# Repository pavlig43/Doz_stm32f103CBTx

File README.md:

# Дозатор: F103 и F030

Общая логика лежит в `app/` и `lib/`. Весь проект CubeMX для каждого МК хранится в своей папке.

```text
app/                         общая логика
lib/                         общие заголовки и модули
  fee/fee.h                  общий интерфейс памяти
  fee/fee.c                  общий модуль памяти
  enc/enc.h                  общий интерфейс энкодера
  enc/enc.c                  общий модуль энкодера
  hx/hx.h, hx/hx.c            один общий модуль HX711
stm32f103/                   проект CubeMX и сборка F103
stm32f030/                   проект CubeMX и сборка F030
kicad/                       проект платы, библиотеки, модели и PDF для ЛУТ
CMakeLists.txt               сборка из корня для CLion
CMakePresets.json            профили F103 и F030
```

В `stm32f103/` находятся `.ioc`, `.mxproject`, `Core/`, `Drivers/`, `cmake/`, файл запуска, файл памяти, `CMakeLists.txt` и `CMakePresets.json`. Корень Git, `app/` и `lib/` остаются общими. Старый `build/` в корне не перенесён; новые сборки пишутся в `stm32f103/build/`.

## Сборка F103

Нужны CMake 3.22+, Ninja и Arm GNU Toolchain (`arm-none-eabi-*`) в `PATH`. В CLion работайте в прежнем корне репозитория. Корневой CMake подключает проект выбранного МК; общий код остаётся виден в том же окне. В `.idea/cmake.xml` сохранены профили F103 Debug, F103 Release, F030 Debug и F030 Release для набора инструментов STM32. Общие файлы уже включены в обе цели; добавлять их вручную не нужно. Для командной строки профили называются Debug, Release, F030-Debug и F030-Release. Переключать папки не нужно. Обе платы запускают общий код дозатора.

```powershell
cmake --preset Debug
cmake --build --preset Debug
cmake --preset Release
cmake --build --preset Release
```

При сборке из корня результаты лежат в `stm32f103/build/CLion-Debug` и `stm32f103/build/CLion-Release`; файлы `.elf` — в их подпапке `stm32f103`. Для F030 используются свои каталоги `stm32f030/build/CLion-*`. Каждый проект также можно собирать отдельно его прежними профилями из папки МК. Общие исходники и пути к заголовкам явно заданы в `stm32f103/CMakeLists.txt`. Обе сборки подключают общие `lib/enc/enc.c` и `lib/fee/fee.c`. В блоке `USER CODE` файла `Core/Inc/tim.h` каждой платы задан `ENC_TIMER`: `htim2` для F103 и `htim3` для F030. В `Core/Inc/main.h` задан `EEPROM_START_ADDR`: `0x0800FC00U` для F103 и `0x08003C00U` для F030. Размер страницы FEE — 1 КБ у обеих плат; в файле памяти F030 для кода оставлено 15 КБ.

## CubeMX и общий код

Открывайте `stm32f103/Doz_stm32f103CBTx.ioc` отдельно. При генерации каталог проекта должен быть `stm32f103`, путь к `main.c` — `Core/Src`, инструмент сборки — CMake. Не выбирайте корень репозитория как каталог вывода. `cmake/stm32cubemx/CMakeLists.txt` внутри проекта принадлежит CubeMX; общие файлы подключайте только в проектном `CMakeLists.txt`. Пользовательский код в `Core/` храните в блоках `USER CODE`.

Для штатного CLI CubeMX загружайте перенесённый `.ioc` и сразу запускайте генерацию; отдельная команда `project path` в CubeMX 6.18 добавляет вложенную папку с именем проекта:

```text
config load <полный путь>/stm32f103/Doz_stm32f103CBTx.ioc
project generate
exit
```

Передавайте такой файл команд в CubeMX через `-q`. На изолированной копии проверены генерация и обе сборки: общие файлы, `USER CODE`, CMake и настройки компилятора сохранены. CubeMX объединяет запись начального низкого уровня `Motor_Pin` с остальными выводами GPIOA; поведение не меняется. Ручной комментарий вне `USER CODE` при этом теряется. Исходный `gpio.c` в этом дереве сохранён.

Для F030 уже создан отдельный `stm32f030/stm32f030.ioc`. CubeMX каждого проекта должен писать только в папку своего МК; `app/`, `lib/` и корневой CMake он не должен менять.

Общие модули получают HAL из проектных `main.h`, `tim.h`, `i2c.h`. Обе платы должны дать сигналы `SCK`, `DOUT`, `Motor`, `R`, `G`, `B`, `Enc_But`, дескриптор `hi2c1` для LCD и `htim1` с шагом счётчика 1 мкс для HX711. Выводы F030 выбираются по схеме.

Код дозатора подключён к F030: в `main.c` добавлены запуск модулей и основной цикл. Debug для F030 использует `-Og`, чтобы код вместе с HAL поместился в 15 КБ Flash; сведения для отладки сохранены. Сборки и расход памяти описаны в [инструкции F030](stm32f030/README.md). Работа на плате ещё требует проверки.

## Проект платы

Текущий проект KiCad хранится вместе с прошивкой: [kicad/doz_030.kicad_pro](kicad/doz_030.kicad_pro). После клонирования или `git pull` открывайте этот файл в KiCad 10. Схема, плата, настройки проекта, нужные библиотеки и 3D-модели находятся в репозитории. Пути к местным библиотекам и моделям заданы через `${KIPRJMOD}` и не зависят от прежнего каталога на компьютере.

PDF для ЛУТ и порядок его сборки описаны в [kicad/README.md](kicad/README.md). Устаревшая папка `hardware` удалена; рабочие правки платы нужно делать только в `kicad/`.

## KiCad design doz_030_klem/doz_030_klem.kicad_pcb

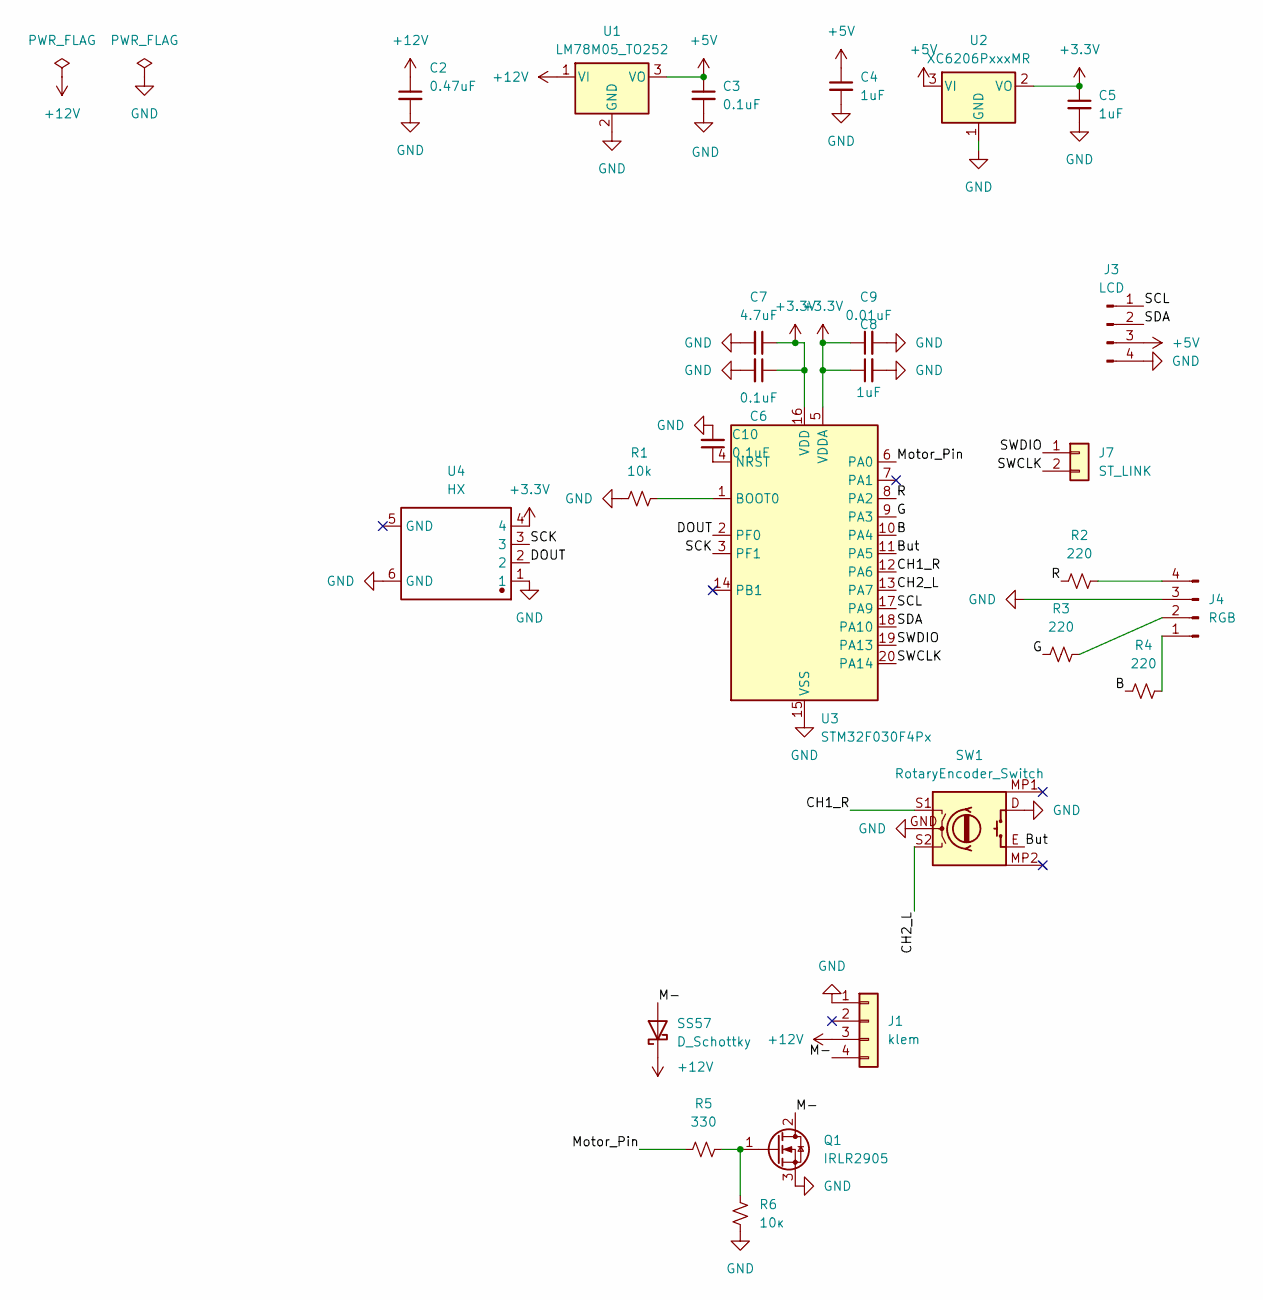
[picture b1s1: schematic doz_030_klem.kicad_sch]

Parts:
C2: 0.47uF; C_1206_3216Metric; Voltage 16V; Tolerance 20%
C3, C6, C10: 0.1uF; C_1206_3216Metric; Voltage 16V; Tolerance 20%
C4, C5, C8: 1uF; C_1206_3216Metric; Voltage 16V; Tolerance 20%
C7: 4.7uF; C_1206_3216Metric; Voltage 16V; Tolerance 20%
C9: 0.01uF; C_1206_3216Metric; Voltage 16V; Tolerance 20%
J1: klem; TerminalBlock_MaiXu_MX126-5.0-04P_1x04_P5.00mm
J3: LCD; PinHeader_1x04_P2.54mm_Vertical
J4: RGB; PinHeader_1x04_P2.54mm_Vertical
J7: ST_LINK; PinHeader_1x02_P2.54mm_Vertical
Q1: IRLR2905; TO-252-2
R1: 10k; R_1206_3216Metric
R2, R3, R4: 220; R_1206_3216Metric
R5: 330; R_1206_3216Metric
R6: 10к; R_1206_3216Metric
SS57: D_Schottky; D_SMC
SW1: RotaryEncoder_Switch; EC11_MY
U1: LM78M05_TO252; TO-252-2
U2: XC6206PxxxMR; SOT-23-3
U3: STM32F030F4Px; TSSOP-20_4.4x6.5mm_P0.65mm
U4: HX; USB_A_TH_MOLEX_67643_3910; Manufacturer Part 67643-3910

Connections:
+3.3V: C5.1, C6.1, C7.1, C8.1, C9.1, U2.2 (VO), U3.5 (VDDA), U3.16 (VDD), U4.4
+5V: C3.1, C4.1, J3.3, U1.3 (VO), U2.3 (VI)
+12V: C2.1, J1.3, SS57.1 (K), U1.1 (VI)
/B: R4.1, U3.10 (PA4)
/But: SW1.E, U3.11 (PA5)
/CH1_R: SW1.S1, U3.12 (PA6)
/CH2_L: SW1.S2, U3.13 (PA7)
/DOUT: U3.2 (PF0), U4.2
/G: R3.1, U3.9 (PA3)
/M-: J1.4, Q1.2 (D), SS57.2 (A)
/Motor_Pin: R5.1, U3.6 (PA0)
/R: R2.1, U3.8 (PA2)
/SCK: U3.3 (PF1), U4.3
/SCL: J3.1, U3.17 (PA9)
/SDA: J3.2, U3.18 (PA10)
/SWCLK: J7.2, U3.20 (PA14); also elsewhere on the board
/SWDIO: J7.1, U3.19 (PA13); also elsewhere on the board
GND: C2.2, C3.2, C4.2, C5.2, C6.2, C7.2, C8.2, C9.2, C10.2, J1.1, J3.4, J4.3, Q1.3 (S), R1.1, R6.1, SW1.D, SW1.GND, U1.2 (GND), U2.1 (GND), U3.15 (VSS), U4.1, U4.6 (GND)
unnamed: J4.1, R4.2
unnamed: J4.2, R3.2
unnamed: J4.4, R2.2
unnamed: Q1.1 (G), R5.2, R6.2
unnamed: R1.2, U3.1 (BOOT0)
unnamed: C10.1, U3.4 (NRST)

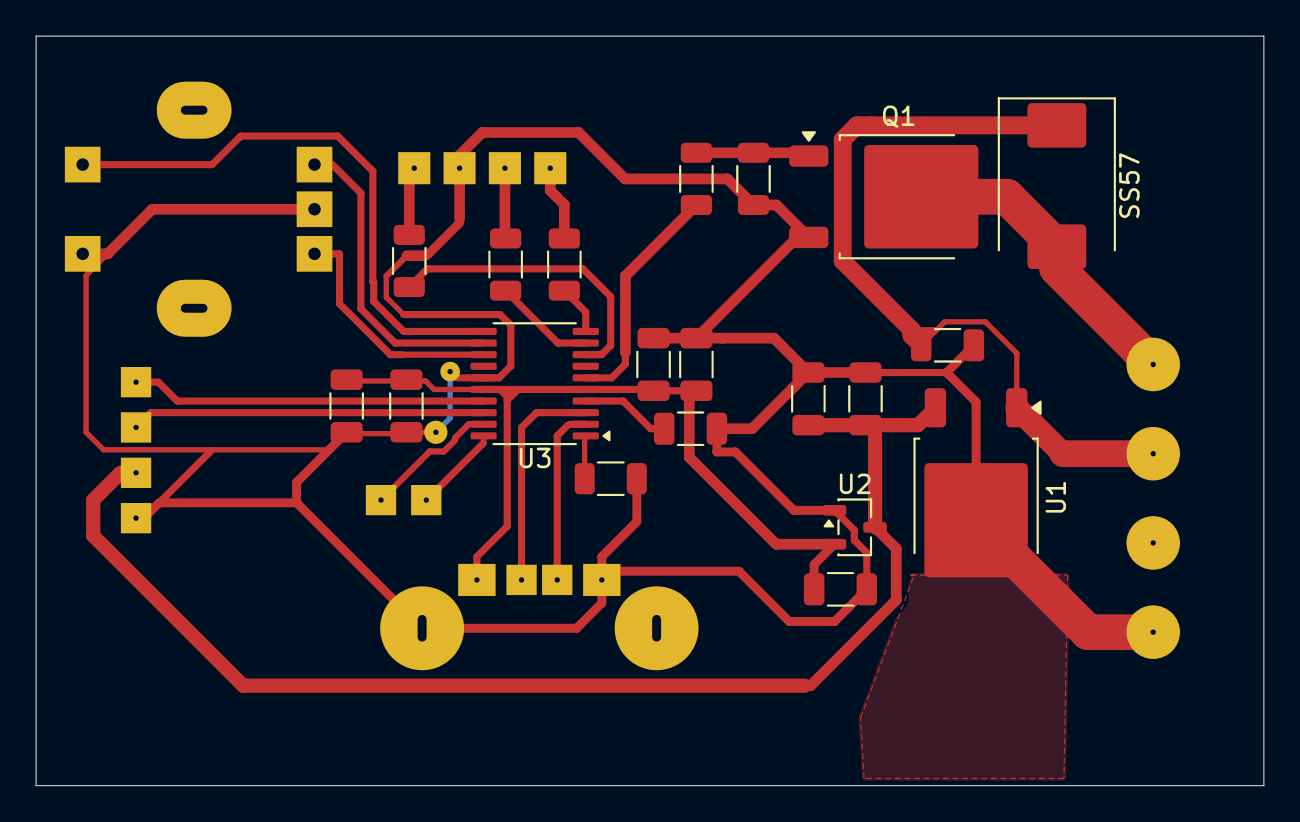
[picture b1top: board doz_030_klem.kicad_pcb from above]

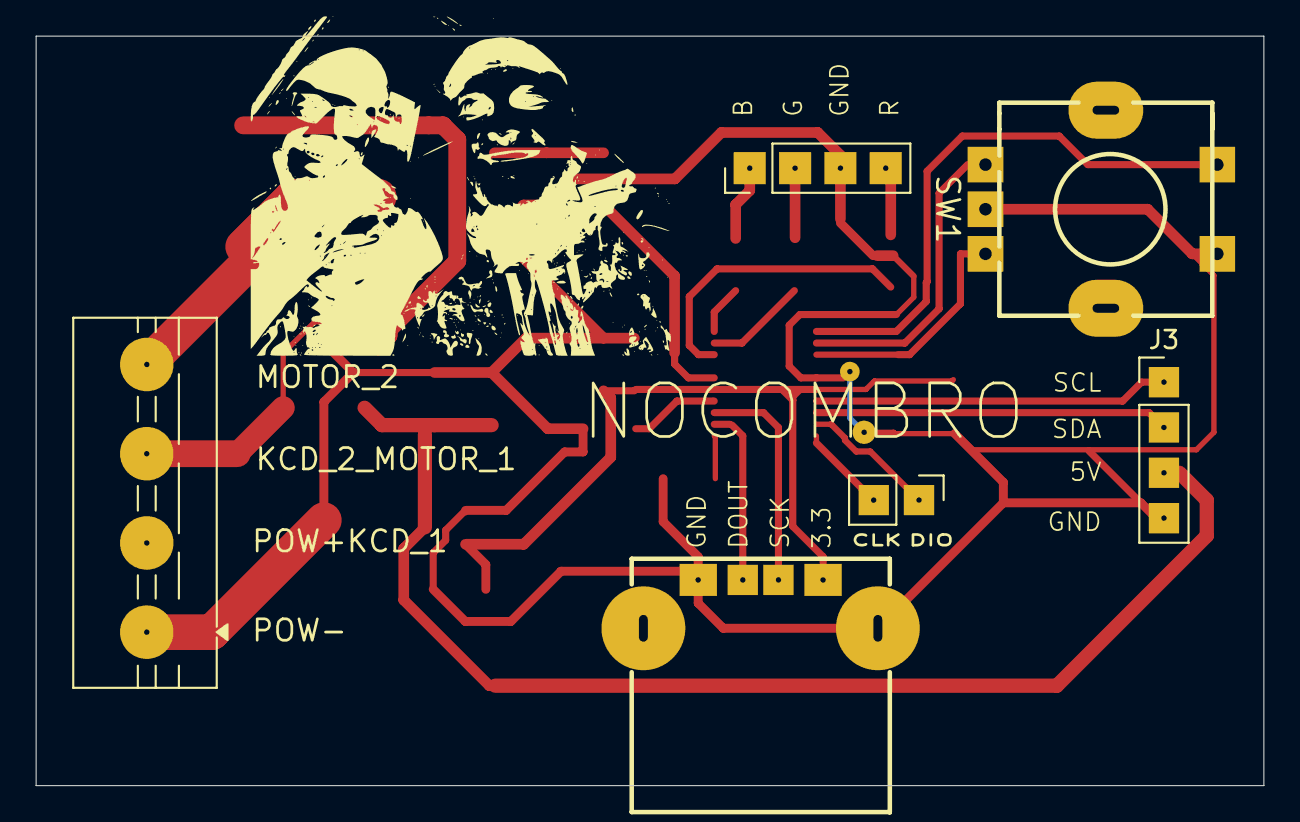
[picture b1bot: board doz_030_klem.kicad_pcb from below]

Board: 2 copper layers, 68.8 x 42.0 mm, 27 parts (7 on the bottom side), 24 nets.

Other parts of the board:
J: ST_LINK; PinHeader_1x02_P2.54mm_Vertical
a: LOGO

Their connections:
/SWCLK: J.2; also elsewhere on the board
/SWDIO: J.1; also elsewhere on the board

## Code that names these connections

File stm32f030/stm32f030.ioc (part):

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Mcu.Name=STM32F030F4Px
Mcu.Package=TSSOP20
Mcu.UserName=STM32F030F4Px
PA0.GPIOParameters=GPIO_Label
PA0.GPIO_Label=Motor
PA0.Signal=GPIO_Output
PA10.Mode=I2C
PA10.Signal=I2C1_SDA
PA13.Mode=Serial_Wire
PA13.Signal=SYS_SWDIO
PA14.Mode=Serial_Wire
PA14.Signal=SYS_SWCLK
PA2.GPIOParameters=GPIO_Label
PA2.GPIO_Label=R
PA2.Signal=GPIO_Output
PA3.GPIOParameters=GPIO_Label
PA3.GPIO_Label=G
PA3.Signal=GPIO_Output
PA4.GPIOParameters=GPIO_Label
PA4.GPIO_Label=B
PA4.Signal=GPIO_Output
PA5.GPIOParameters=GPIO_PuPd,GPIO_Label
PA5.GPIO_Label=Enc_But
PA5.GPIO_PuPd=GPIO_PULLUP
PA5.Signal=GPIO_Input
PA6.GPIOParameters=GPIO_PuPd
PA6.GPIO_PuPd=GPIO_PULLUP
PA6.Signal=S_TIM3_CH1
PA7.GPIOParameters=GPIO_PuPd
PA7.GPIO_PuPd=GPIO_PULLUP
PA7.Signal=S_TIM3_CH2
PA9.Mode=I2C
PA9.Signal=I2C1_SCL
PF0-OSC_IN.GPIOParameters=GPIO_Label
PF0-OSC_IN.GPIO_Label=DOUT
PF0-OSC_IN.Signal=GPIO_Input
PF1-OSC_OUT.GPIOParameters=GPIO_Label
PF1-OSC_OUT.GPIO_Label=SCK
PF1-OSC_OUT.Signal=GPIO_Output
RCC.SYSCLKFreq_VALUE=48000000
RCC.SYSCLKSource=RCC_SYSCLKSOURCE_PLLCLK
board=custom
